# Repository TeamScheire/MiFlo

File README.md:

# Team Scheire MiFlo's voor Minne en Flo

Met hun MiFlo kregen Minne en Flo hun eigen persoonlijke digitale assistent.

De MiFlo is een wekker die aan het internet hangt. Mama en papa kunnen via chat of hun online kalender todo's, herinneringen, wekkers of time-timers klaarzetten voor de kinderen.

Door opdrachtjes uit te voeren krijgen de kinderen punten en "gamifyen" we hun dagdagelijkse schema.

Deze repository bevat alle onderdelen die je nodig hebt om zelf een MiFlo te bouwen. 

Een beetje handigheid met Arduino's en elektronische componenten is wel nodig als je zelf een miflo wekker wil maken.

* Onder [hardware](./hardware) kan je een BOM vinden van de materialen die gebruikt werden. Het bevat ook het PCB design en de files om de 3D prints te maken.
* Onder [arduino](./arduino) kan je de code vinden die op de MiFlo's draait. 
* Onder [assets](./assets) vind je de iconen en geluiden die op de SD kaart van de MiFlo staan.
* Onder [backend](./backend) vind je de code die de MiFlo's vanuit het internet controleert. Je kan met Telegram opdrachten naar de MiFlo sturen. Of je kan in Google calendar opdrachten klaarzetten die dan elke 5 minuten worden opgehaald en doorgegeven worden aan de MiFlo's.

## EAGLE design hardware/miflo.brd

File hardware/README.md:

# Hardware voor de MiFlo

De hardware in de MiFlo is opgebouwd op eenvoudig verkrijgbare modules:

* In het originele project wordt een [Adafruit Feather HUZZAH](https://learn.adafruit.com/adafruit-feather-huzzah-esp8266) gebruikt als de "Arduino". Deze bevat een ESP8266 chip waarmee we ook WiFi kunnen gebruiken. Zijn opvolger, de [Adafruit Feather HUZZAH32](https://learn.adafruit.com/adafruit-huzzah32-esp32-feather) kan echter ook gebruikt worden. Deze is een pak krachtiger en bovendien een beetje zuiniger in verbruik.
* De [Gameduino 3](http://excamera.com/sphinx/gameduino3/) is een touchscreen dat je makkelijk op een Arduino kan monteren en aansturen. Het kan ook geluiden of filmpjes spelen van een SD kaart. Bijvoorbeeld [hier te koop](https://www.watterott.com/de/Gameduino-3).
  * Een micro SD kaart voor de [assets](../assets) van het MiFlo programma. Let op dat je betrouwbare SD-kaart koopt, want de gameduino kan problemen hebben met goedkopere of witte merken. Met een SanDisk of Kingston kan je normaal weinig mis doen.
* Met een [RTC breakout board](https://www.adafruit.com/product/3295) kunnen we de tijd bijhouden als de MiFlo geen stroom heeft.
* Een [geluidsversterker](https://www.adafruit.com/product/1752) zorgt ervoor dat de audio krachtig genoeg uit de speakers komt.
* We bouwden alles in een [SoundLogic draagbare speaker](https://www.action.com/nl-be/p/soundlogic-draagbare-speaker/) van den Action.

We ontwierpen zelf een PCB die deze componenten allemaal bij elkaar brengt, deze vind je (als `.brd` en `.sch` files voor Autodesk EAGLE) in deze repository. Met de PCB kan je zowel een klassieke Arduino of een Adafruit Feather verbinden met het Gameduino touchscreen.

Om de MiFlo mooi te bevestigen printten we kittenoortjes voor Minne en een Lego-helm voor Flo. Samen met 2 clips kan je de MiFlo zo bevestigen in de draagbare speakerkast. Je vindt deze STL files om zelf te printen als `kat.stl`, `legohelm.stl` en `clip.stl`.

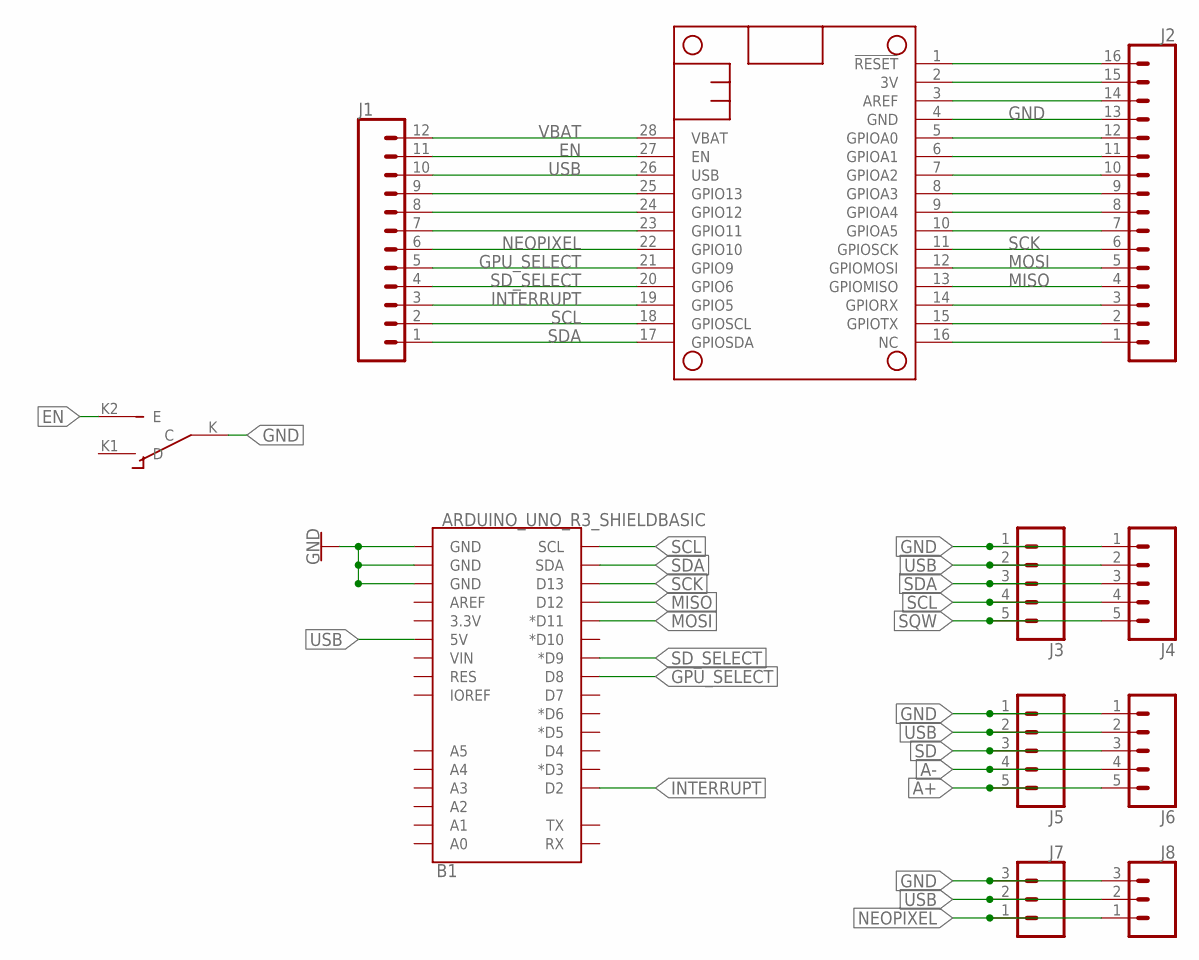
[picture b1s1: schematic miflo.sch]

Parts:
B1: ARDUINO_UNO_R3_SHIELDBASIC; UNO_R3_SHIELD
J1: CONN_12; 1X12
J2: CONN_16; 1X16
J3, J4, J5, J6: CONN_05; 1X05
J7, J8: CONN_03; 1X03
MS2: FEATHERWING_NODIM; FEATHERWING_DIM
U$11: SLIDE-SWITCH

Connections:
3V: J2.15, MS2.2 (3V)
A+: J5.5, J6.5
A-: J5.4, J6.4
EN: J1.11, MS2.27 (EN), U$11.K2 (E)
GND: B1.GND@0 (GND), B1.GND@1 (GND), B1.GND@2 (GND), J2.13, J3.1, J4.1, J5.1, J6.1, J7.3, J8.3, MS2.4 (GND), U$11.K (C)
GPU_SELECT: B1.D8, J1.5, MS2.21 (GPIO9)
INTERRUPT: B1.D2, J1.3, MS2.19 (GPIO5)
MISO: B1.D12, J2.4, MS2.13 (GPIOMISO)
MOSI: B1.D11 (*D11), J2.5, MS2.12 (GPIOMOSI)
unnamed: J1.9, MS2.25 (GPIO13)
unnamed: J1.8, MS2.24 (GPIO12)
unnamed: J1.7, MS2.23 (GPIO11)
unnamed: J2.1, MS2.16 (NC)
unnamed: J2.2, MS2.15 (GPIOTX)
unnamed: J2.3, MS2.14 (GPIORX)
unnamed: J2.7, MS2.10 (GPIOA5)
unnamed: J2.8, MS2.9 (GPIOA4)
unnamed: J2.9, MS2.8 (GPIOA3)
unnamed: J2.10, MS2.7 (GPIOA2)
unnamed: J2.11, MS2.6 (GPIOA1)
unnamed: J2.12, MS2.5 (GPIOA0)
unnamed: J2.14, MS2.3 (AREF)
unnamed: J2.16, MS2.1 (!RESET)
NEOPIXEL: J1.6, J7.1, J8.1, MS2.22 (GPIO10)
SCK: B1.D13, J2.6, MS2.11 (GPIOSCK)
SCL: B1.SCL, J1.2, J3.4, J4.4, MS2.18 (GPIOSCL)
SD: J5.3, J6.3
SDA: B1.SDA, J1.1, J3.3, J4.3, MS2.17 (GPIOSDA)
SD_SELECT: B1.D9 (*D9), J1.4, MS2.20 (GPIO6)
SQW: J3.5, J4.5
USB: B1.5V, J1.10, J3.2, J4.2, J5.2, J6.2, J7.2, J8.2, MS2.26 (USB)
VBAT: J1.12, MS2.28 (VBAT)

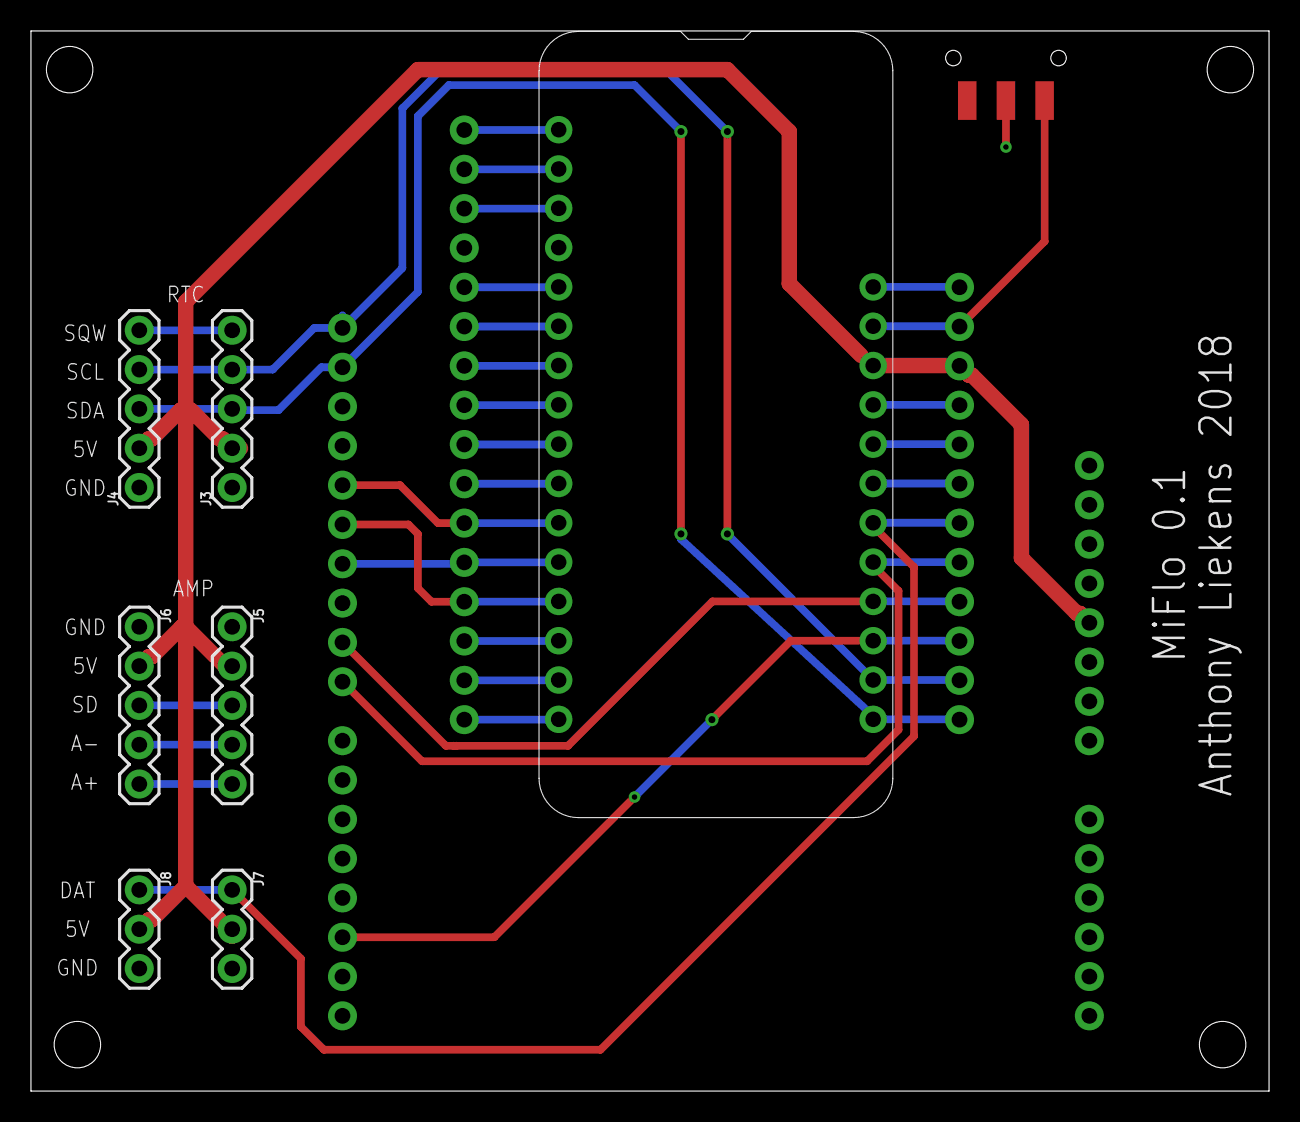
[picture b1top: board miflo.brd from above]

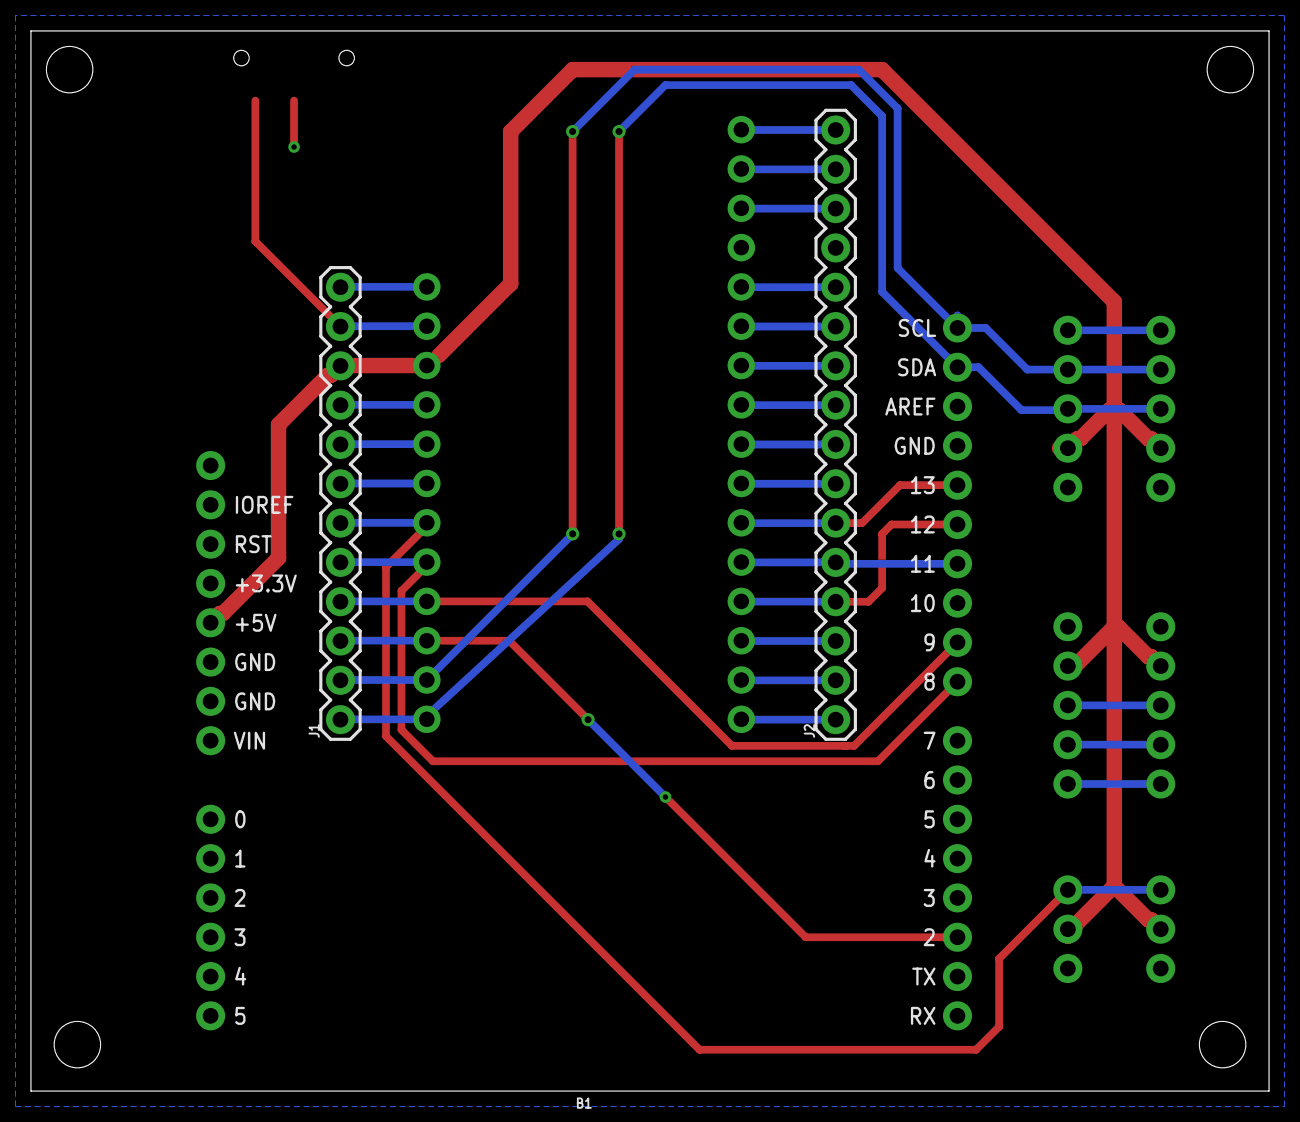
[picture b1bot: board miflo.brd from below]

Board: 2 copper layers, 80.0 x 68.5 mm, 11 parts (3 on the bottom side), 32 nets.

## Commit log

2018-04-20 initial commit, needs LOTS of cleaning up
2018-04-20 show clock after booting
2018-04-20 separate function to play jingles and mute everything else
2018-04-20 MQTT reconnect on disconnect
2018-04-20 only show upcoming events when there are any available
2018-04-26 simplest way to define a person is to hardcode it ...
2018-04-26 set the clock
2018-04-26 support new icon set by pixer
2018-04-26 a first few tests with audio
2018-05-01 updated audio, new reminders
2018-05-01 cleaner states and introduction of alarm state
2018-05-01 jpegs en betere timetimers
2018-05-01 todo command and various cleanups
2018-05-04 reset points at 1 at night
2018-05-04 motivatiegeluidje bij pluspunt
2018-05-04 odds and ends, ie, control shutdown of speaker with pin 15
2018-05-04 dirty hack to play a sample after the next frame is rendered
2018-05-04 more of the same shenanigans
2018-12-03 arduino code
2018-12-03 assets added
2018-12-03 backend
2018-12-03 licence added
2018-12-03 hardware BOM en PCB
2018-12-03 juiste links
2018-12-03 3d print files
2018-12-03 arduino readme
2018-12-03 root readme
2018-12-03 CC AT-NC license
2018-12-03 readme updates
2018-12-04 gameduino weblink added
2018-12-05 rpi tutorial for backend
2018-12-05 telegram script more generic
2018-12-05 telemgram readme
2018-12-07 intro on readme backend
2018-12-09 update of arduino readme and settings example
2018-12-11 adapt readme to show needed changes to gd2 lib
2018-12-11 fixed asset path in readme
2018-12-12 correct GD.start options
2018-12-12 output ruby to log
2018-12-12 fix path
2018-12-12 backend readme
2019-03-25 Add missing information to instructions
2019-04-03 Add ESP32 chipset instructions
2019-04-03 Correct markdown syntax
2019-04-03 Add link to ESP32 overview and clarify a other things
2019-04-03 Add SD card to hardware requirements
2019-04-03 correct typo
2019-04-03 Add ESP32 SD pin
2019-04-03 Fix core dump on int2char call
2019-04-03 Fix core dump on empty event task
2019-04-03 Use ESP32 wifi library on ESP32
2019-04-04 Change audio amp pin on ESP32

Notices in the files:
parts and their libraries:
SparkFun-Boards: Licensing: Creative Commons ShareAlike 4.0 International - https://creativecommons.org/licenses/by-sa/4.0
